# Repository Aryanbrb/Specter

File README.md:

# Dolivo

Dolivo is a compact, solder-down system-on-module built around the Raspberry Pi RP2350B. It is designed for carrier boards that need the MCU, flash, PSRAM, clock, and core power supply in one assembly. Dolivo uses its own 64-contact inset LGA with a provisional 26 × 16.7 mm outline.

## Hardware

- 16 MB Winbond W25Q128JVPIQ QSPI flash and 8 MB AP Memory APS6404L-3SQR-ZR PSRAM share the QSPI bus. GPIO0 selects the PSRAM.
- A 12 MHz crystal provides the clock. USB, SWD, RUN, and BOOTSEL signals are intended for programming and recovery from the carrier.
- The default assembly takes 5 V through an AP2112K regulator. Fit R7 for this variant. A carrier with regulated 3.3 V uses R8 instead. Populate exactly one link.
- GPIO1 through GPIO47 are labeled in the schematic. The draft [carrier pinout](LGA-Pinout.md) assigns all 47 to module lands.

## Design status

The schematic and prototype BOM are in development. The A4 interface symbol and mating footprints are available for placement trials. The underside contacts use four inset, two-row groups with 0.8 mm square lands at 1.5 mm pitch. The new outline reduces board area by 8.8% while retaining all component placements; earlier carrier footprints must be replaced with A4. Routing, assembly and hardware verification are pending.

## Project files

Open [the KiCad project](Dolivo.kicad_pro) in KiCad 10 to inspect the [schematic](Dolivo.kicad_sch). Keep the project footprint table and [local footprint library](SoM.pretty/) together so KiCad can resolve the core regulator inductor.

The [BOM and prototype budget](Memory-BOM.md) document component selections, assembly options, and estimated costs for ten modules.

Keep the [project 3D models](3dmodels/README.md) alongside the PCB for the RP2350B and inductor. Install KiCad 10's standard 3D model libraries for the remaining components.

## Open hardware

Dolivo is preparing its first hardware revision for OSHWA certification. The original hardware is licensed under CERN-OHL-W-2.0 and the original documentation under CC BY 4.0. See the [licensing scope and third-party notices](LICENSING.md) and the [Rev A release checklist](OPEN-HARDWARE.md). Certification is pending a completed release and application.

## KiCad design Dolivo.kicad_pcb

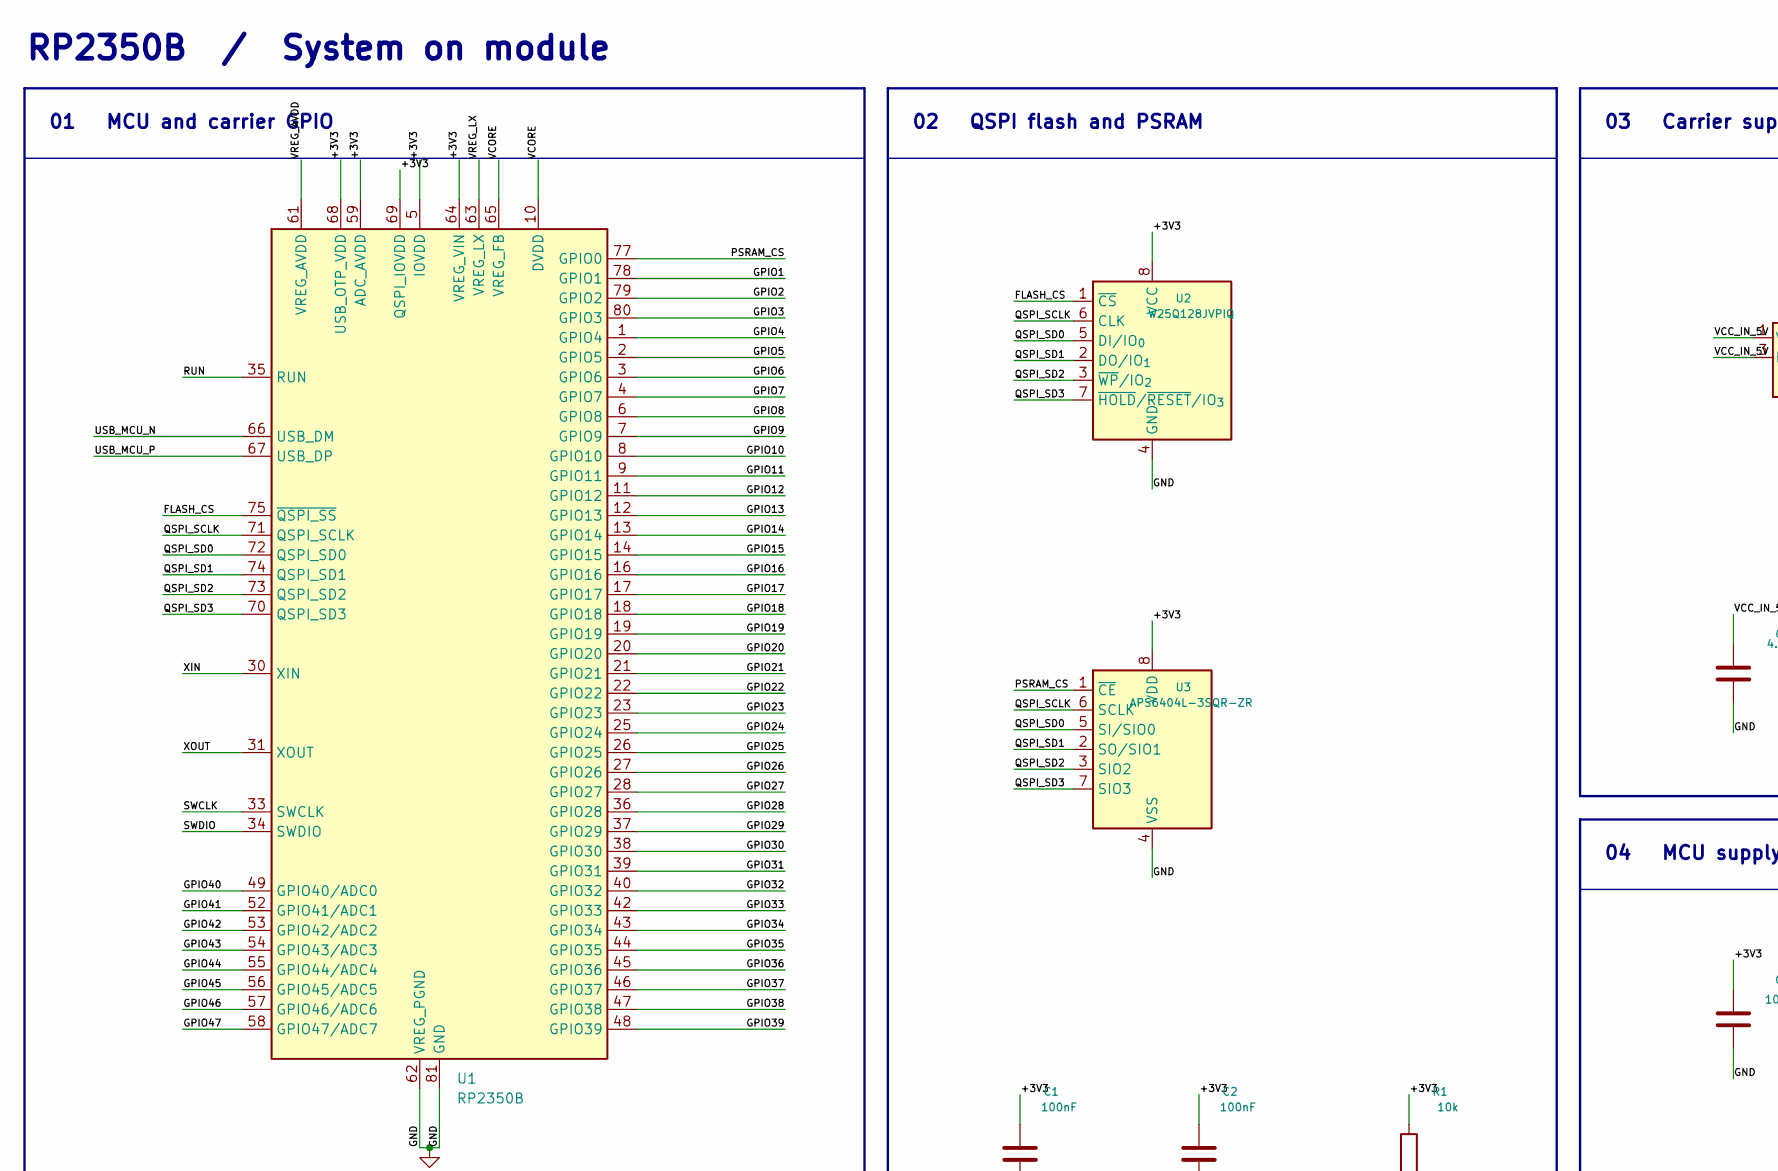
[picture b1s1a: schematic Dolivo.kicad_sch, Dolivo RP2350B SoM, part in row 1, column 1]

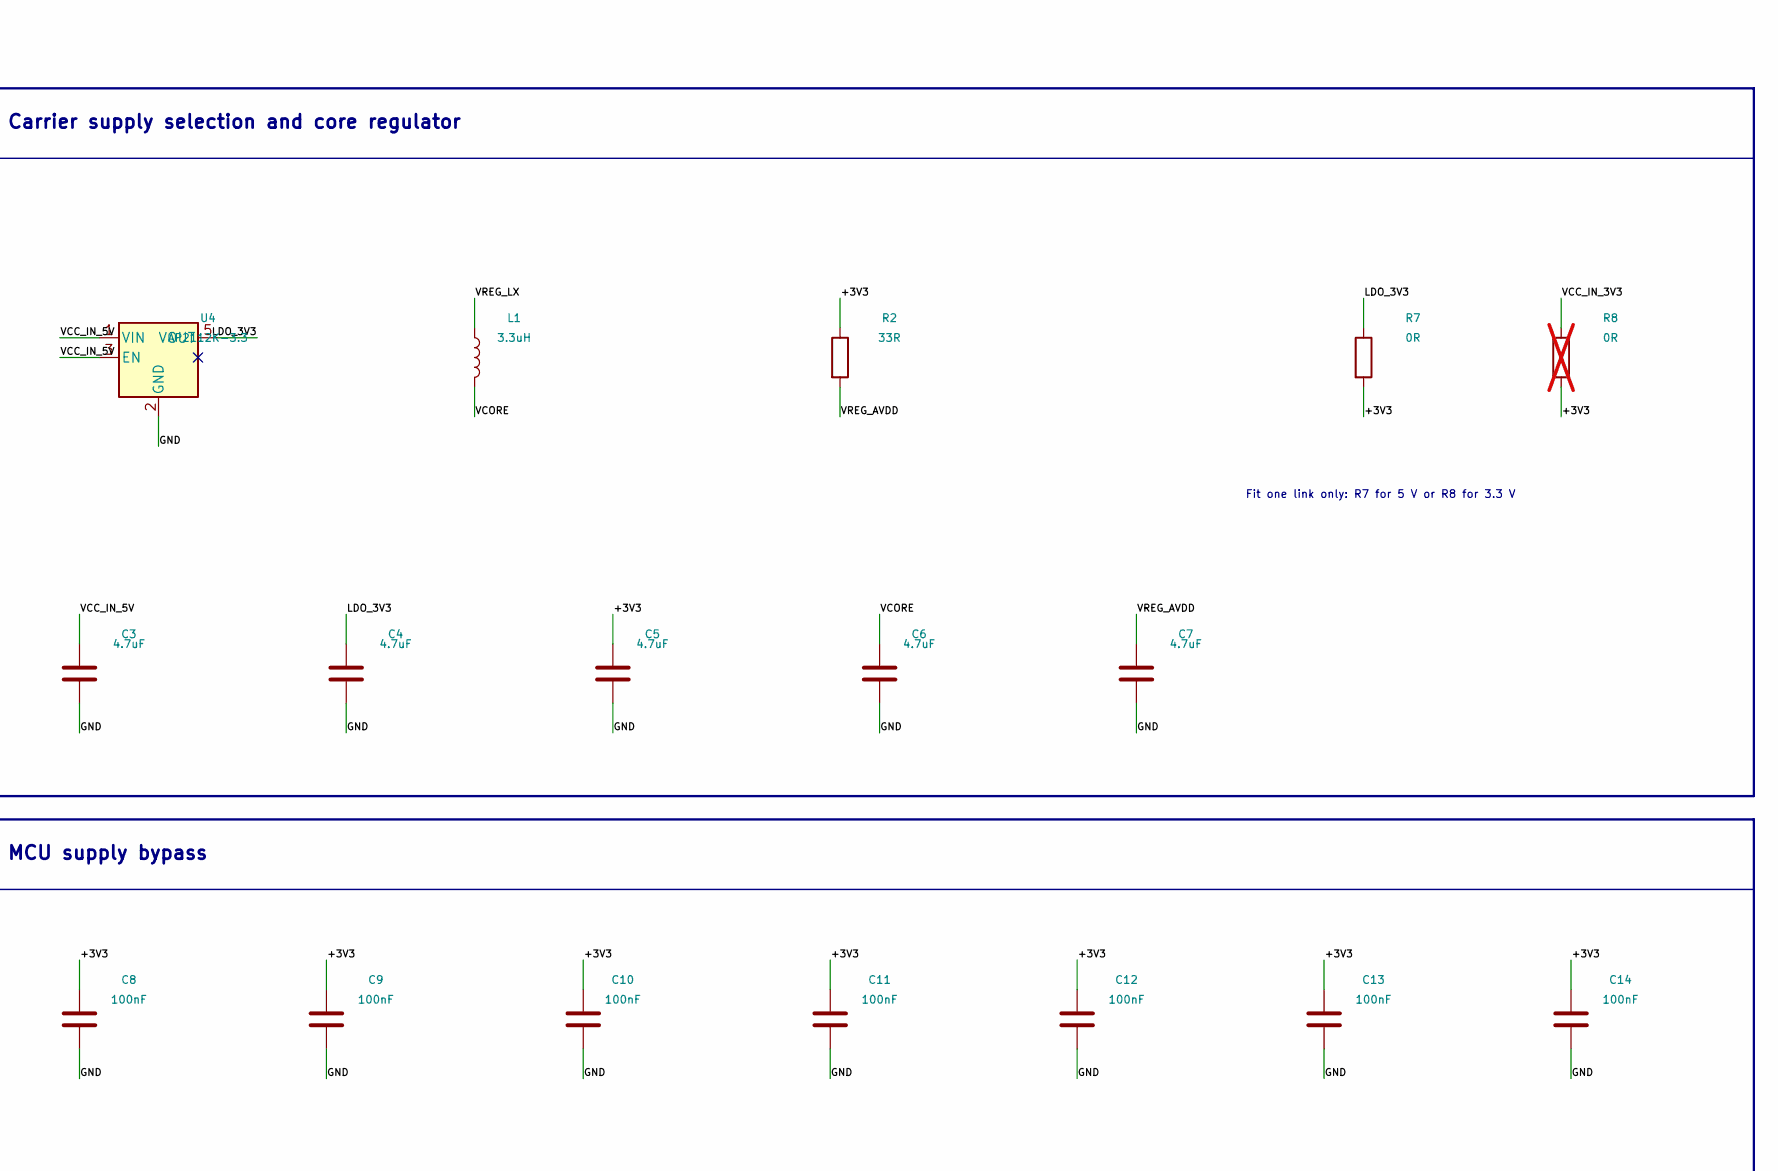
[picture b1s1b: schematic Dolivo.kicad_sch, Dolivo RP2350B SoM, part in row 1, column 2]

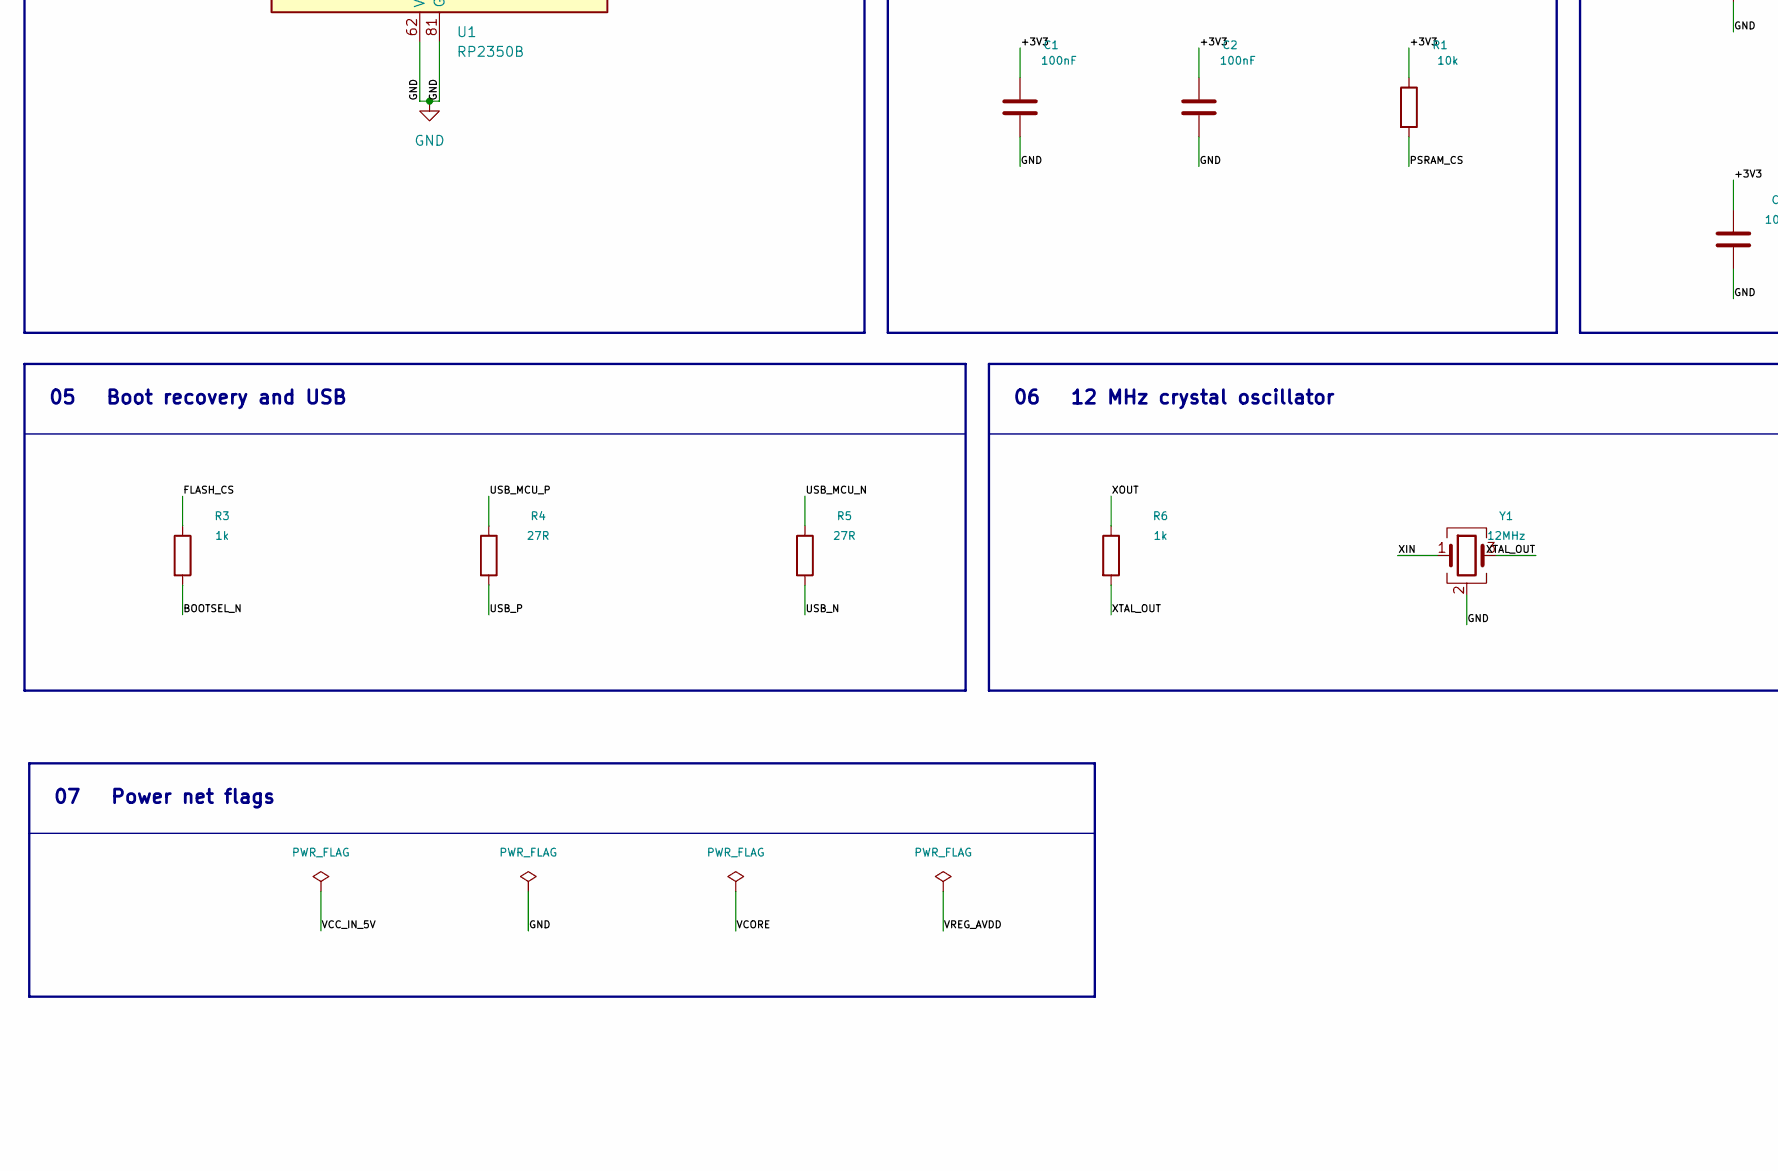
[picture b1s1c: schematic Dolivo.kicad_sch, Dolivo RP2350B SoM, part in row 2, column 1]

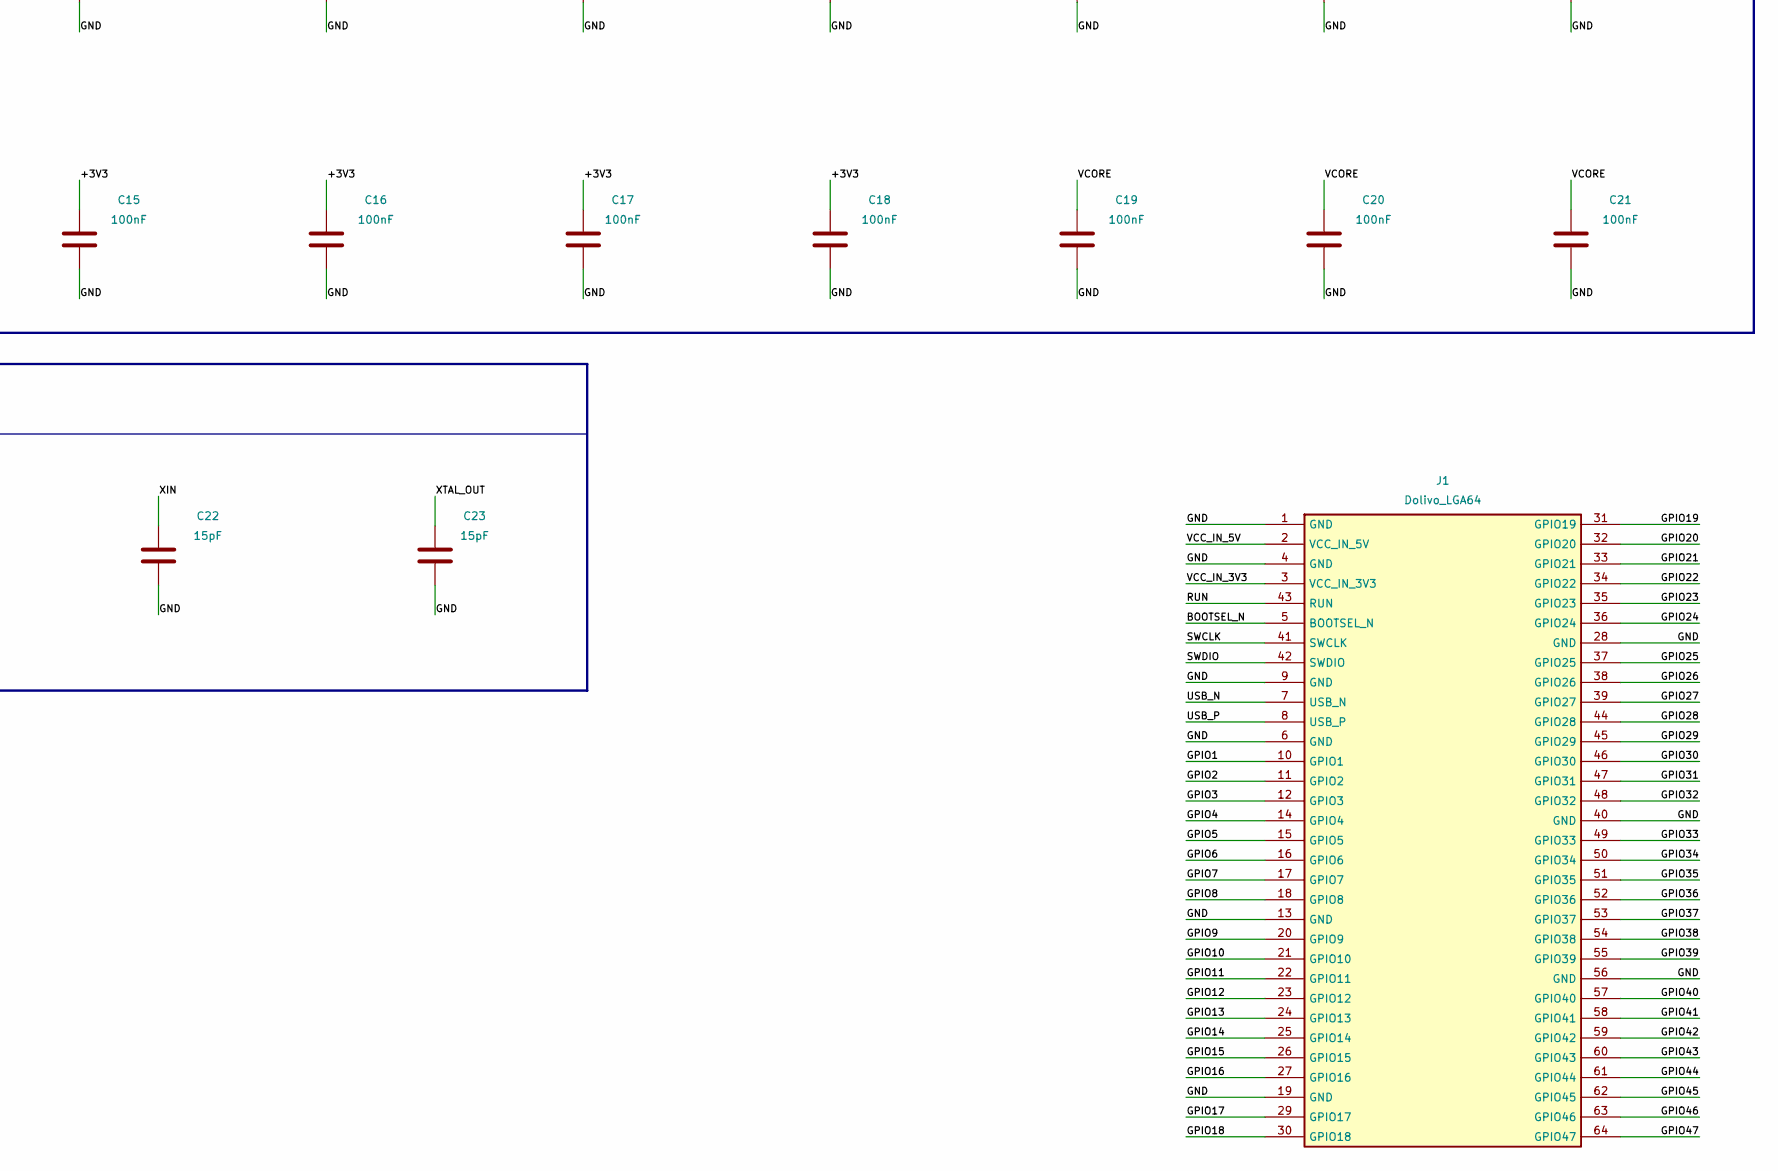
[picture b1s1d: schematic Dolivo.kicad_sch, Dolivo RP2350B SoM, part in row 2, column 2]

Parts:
C1, C2, C8, C9, C10, C11, C12, C13, C14, C15, C16, C17, C18, C19, C20, C21: 100nF; C_0402_1005Metric; MPN CC0402KRX7R7BB104
C3, C4, C5, C6, C7: 4.7uF; C_0402_1005Metric; MPN GRM155R61A475MEAAD
C22, C23: 15pF; C_0402_1005Metric; MPN CC0402JRNPO9BN150
J1: Dolivo_LGA64; Dolivo_LGA64_Module
L1: 3.3uH; AOTA-B201610S3R3-101-T; MPN AOTA-B201610S3R3-101-T
R1: 10k; R_0402_1005Metric; MPN RC0402FR-0710KL
R2: 33R; R_0402_1005Metric; MPN RC0402FR-0733RL
R3, R6: 1k; R_0402_1005Metric; MPN RC0402FR-071KL
R4, R5: 27R; R_0402_1005Metric; MPN RC0402FR-0727RL
R7: 0R; R_0402_1005Metric; MPN RC0402JR-070RL
R8: 0R; R_0402_1005Metric; MPN RC0402JR-070RL; not fitted
U1: RP2350B; QFN-80-1EP_10x10mm_P0.4mm_EP3.4x3.4mm
U2: W25Q128JVPIQ; WSON-8-1EP_6x5mm_P1.27mm_EP3.4x4.3mm; MPN W25Q128JVPIQ
U3: APS6404L-3SQR-ZR; Winbond_USON-8-1EP_3x2mm_P0.5mm_EP0.2x1.6mm; MPN APS6404L-3SQR-ZR
U4: AP2112K-3.3; SOT-23-5; MPN AP2112K-3.3TRG1
Y1: 12MHz; Crystal_SMD_3225-4Pin_3.2x2.5mm; MPN ABM8-272-T3

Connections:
/+3V3: C1.1, C2.1, C5.1, C8.1, C9.1, C10.1, C11.1, C12.1, C13.1, C14.1, C15.1, C16.1, C17.1, C18.1, R1.1, R2.1, R7.2, R8.2, U1.5 (IOVDD), U1.15 (IOVDD), U1.24 (IOVDD), U1.29 (IOVDD), U1.41 (IOVDD), U1.50 (IOVDD), U1.59 (ADC_AVDD), U1.60 (IOVDD), U1.64 (VREG_VIN), U1.68 (USB_OTP_VDD), U1.69 (QSPI_IOVDD), U1.76 (IOVDD), U2.8 (VCC), U3.8 (VDD)
/BOOTSEL_N: J1.5 (RUN), R3.2
/FLASH_CS: R3.1, U1.75 (~QSPI_SS), U2.1 (~CS)
/GPIO1: J1.10 (USB_DM), U1.78 (GPIO1)
/GPIO2: J1.11 (USB_DP), U1.79 (GPIO2)
/GPIO3: J1.12 (GND), U1.80 (GPIO3)
/GPIO4: J1.14 (GPIO2), U1.1 (GPIO4)
/GPIO5: J1.15 (GPIO3), U1.2 (GPIO5)
/GPIO6: J1.16 (GPIO4), U1.3 (GPIO6)
/GPIO7: J1.17 (GPIO5), U1.4 (GPIO7)
/GPIO8: J1.18 (GPIO6), U1.6 (GPIO8)
/GPIO9: J1.20 (GPIO8), U1.7 (GPIO9)
/GPIO10: J1.21 (GND), U1.8 (GPIO10)
/GPIO11: J1.22 (GPIO9), U1.9 (GPIO11)
/GPIO12: J1.23 (GPIO10), U1.11 (GPIO12)
/GPIO13: J1.24 (GPIO11), U1.12 (GPIO13)
/GPIO14: J1.25 (GPIO12), U1.13 (GPIO14)
/GPIO15: J1.26 (GPIO13), U1.14 (GPIO15)
/GPIO16: J1.27 (GPIO14), U1.16 (GPIO16)
/GPIO17: J1.29 (GPIO16), U1.17 (GPIO17)
/GPIO18: J1.30 (GND), U1.18 (GPIO18)
/GPIO19: J1.31 (GPIO17), U1.19 (GPIO19)
/GPIO20: J1.32 (GPIO18), U1.20 (GPIO20)
/GPIO21: J1.33 (GPIO19), U1.21 (GPIO21)
/GPIO22: J1.34 (GPIO20), U1.22 (GPIO22)
/GPIO23: J1.35 (GPIO21), U1.23 (GPIO23)
/GPIO24: J1.36 (GPIO22), U1.25 (GPIO24)
/GPIO25: J1.37 (GPIO23), U1.26 (GPIO25)
/GPIO26: J1.38 (GPIO24), U1.27 (GPIO26)
/GPIO27: J1.39 (GND), U1.28 (GPIO27)
/GPIO28: J1.44 (GPIO29), U1.36 (GPIO28)
/GPIO29: J1.45 (GPIO30), U1.37 (GPIO29)
/GPIO30: J1.46 (GPIO31), U1.38 (GPIO30)
/GPIO31: J1.47 (GPIO32), U1.39 (GPIO31)
/GPIO32: J1.48 (GND), U1.40 (GPIO32)
/GPIO33: J1.49 (GPIO33), U1.42 (GPIO33)
/GPIO34: J1.50 (GPIO34), U1.43 (GPIO34)
/GPIO35: J1.51 (GPIO35), U1.44 (GPIO35)
/GPIO36: J1.52 (GPIO36), U1.45 (GPIO36)
/GPIO37: J1.53 (GPIO37), U1.46 (GPIO37)
/GPIO38: J1.54 (GPIO38), U1.47 (GPIO38)
/GPIO39: J1.55 (GPIO39), U1.48 (GPIO39)
/GPIO40: J1.57 (GPIO40), U1.49 (GPIO40/ADC0)
/GPIO41: J1.58 (GPIO41), U1.52 (GPIO41/ADC1)
/GPIO42: J1.59 (GPIO42), U1.53 (GPIO42/ADC2)
/GPIO43: J1.60 (GPIO43), U1.54 (GPIO43/ADC3)
/GPIO44: J1.61 (GPIO44), U1.55 (GPIO44/ADC4)
/GPIO45: J1.62 (GPIO45), U1.56 (GPIO45/ADC5)
/GPIO46: J1.63 (GPIO46), U1.57 (GPIO46/ADC6)
/GPIO47: J1.64 (GPIO47), U1.58 (GPIO47/ADC7)
/LDO_3V3: C4.1, R7.1, U4.5 (VOUT)
/PSRAM_CS: R1.2, U1.77 (GPIO0), U3.1 (~CE)
/QSPI_SCLK: U1.71 (QSPI_SCLK), U2.6 (CLK), U3.6 (SCLK)
/QSPI_SD0: U1.72 (QSPI_SD0), U2.5 (DI/IO_{0}), U3.5 (SI/SIO0)
/QSPI_SD1: U1.74 (QSPI_SD1), U2.2 (DO/IO_{1}), U3.2 (SO/SIO1)
/QSPI_SD2: U1.73 (QSPI_SD2), U2.3 (~WP/IO_{2}), U3.3 (SIO2)
/QSPI_SD3: U1.70 (QSPI_SD3), U2.7 (~HOLD/~RESET/IO_{3}), U3.7 (SIO3)
/RUN: J1.43 (GPIO28), U1.35 (RUN)
/SWCLK: J1.41 (GPIO26), U1.33 (SWCLK)
/SWDIO: J1.42 (GPIO27), U1.34 (SWDIO)
/USB_MCU_N: R5.1, U1.66 (USB_DM)
/USB_MCU_P: R4.1, U1.67 (USB_DP)
/USB_N: J1.7 (SWCLK), R5.2
/USB_P: J1.8 (SWDIO), R4.2
/VCC_IN_3V3: J1.3 (GND), R8.1
/VCC_IN_5V: C3.1, J1.2 (VCC_IN_5V), U4.1 (VIN), U4.3 (EN)
/VCORE: C6.1, C19.1, C20.1, C21.1, L1.2, U1.10 (DVDD), U1.32 (DVDD), U1.51 (DVDD), U1.65 (VREG_FB)
/VREG_AVDD: C7.1, R2.2, U1.61 (VREG_AVDD)
/VREG_LX: L1.1, U1.63 (VREG_LX)
/XIN: C22.1, U1.30 (XIN), Y1.1
/XOUT: R6.1, U1.31 (XOUT)
/XTAL_OUT: C23.1, R6.2, Y1.3
GND: C1.2, C2.2, C3.2, C4.2, C5.2, C6.2, C7.2, C8.2, C9.2, C10.2, C11.2, C12.2, C13.2, C14.2, C15.2, C16.2, C17.2, C18.2, C19.2, C20.2, C21.2, C22.2, C23.2, J1.1 (GND), J1.4 (VCC_IN_3V3), J1.6 (BOOTSEL_N), J1.9 (GND), J1.13 (GPIO1), J1.19 (GPIO7), J1.28 (GPIO15), J1.40 (GPIO25), J1.56 (GND), U1.62 (VREG_PGND), U1.81 (GND), U2.4 (GND), U3.4 (VSS), U4.2 (GND), Y1.2 (G), Y1.4 (G)

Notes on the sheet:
RP2350B / System on module
06 12 MHz crystal oscillator
04 MCU supply bypass
03 Carrier supply selection and core regulator
07 Power net flags
05 Boot recovery and USB
01 MCU and carrier GPIO
02 QSPI flash and PSRAM
Fit one link only: R7 for 5 V or R8 for 3.3 V

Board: 4 copper layers, 38 parts (0 on the bottom side), 73 nets, no tracks yet.
